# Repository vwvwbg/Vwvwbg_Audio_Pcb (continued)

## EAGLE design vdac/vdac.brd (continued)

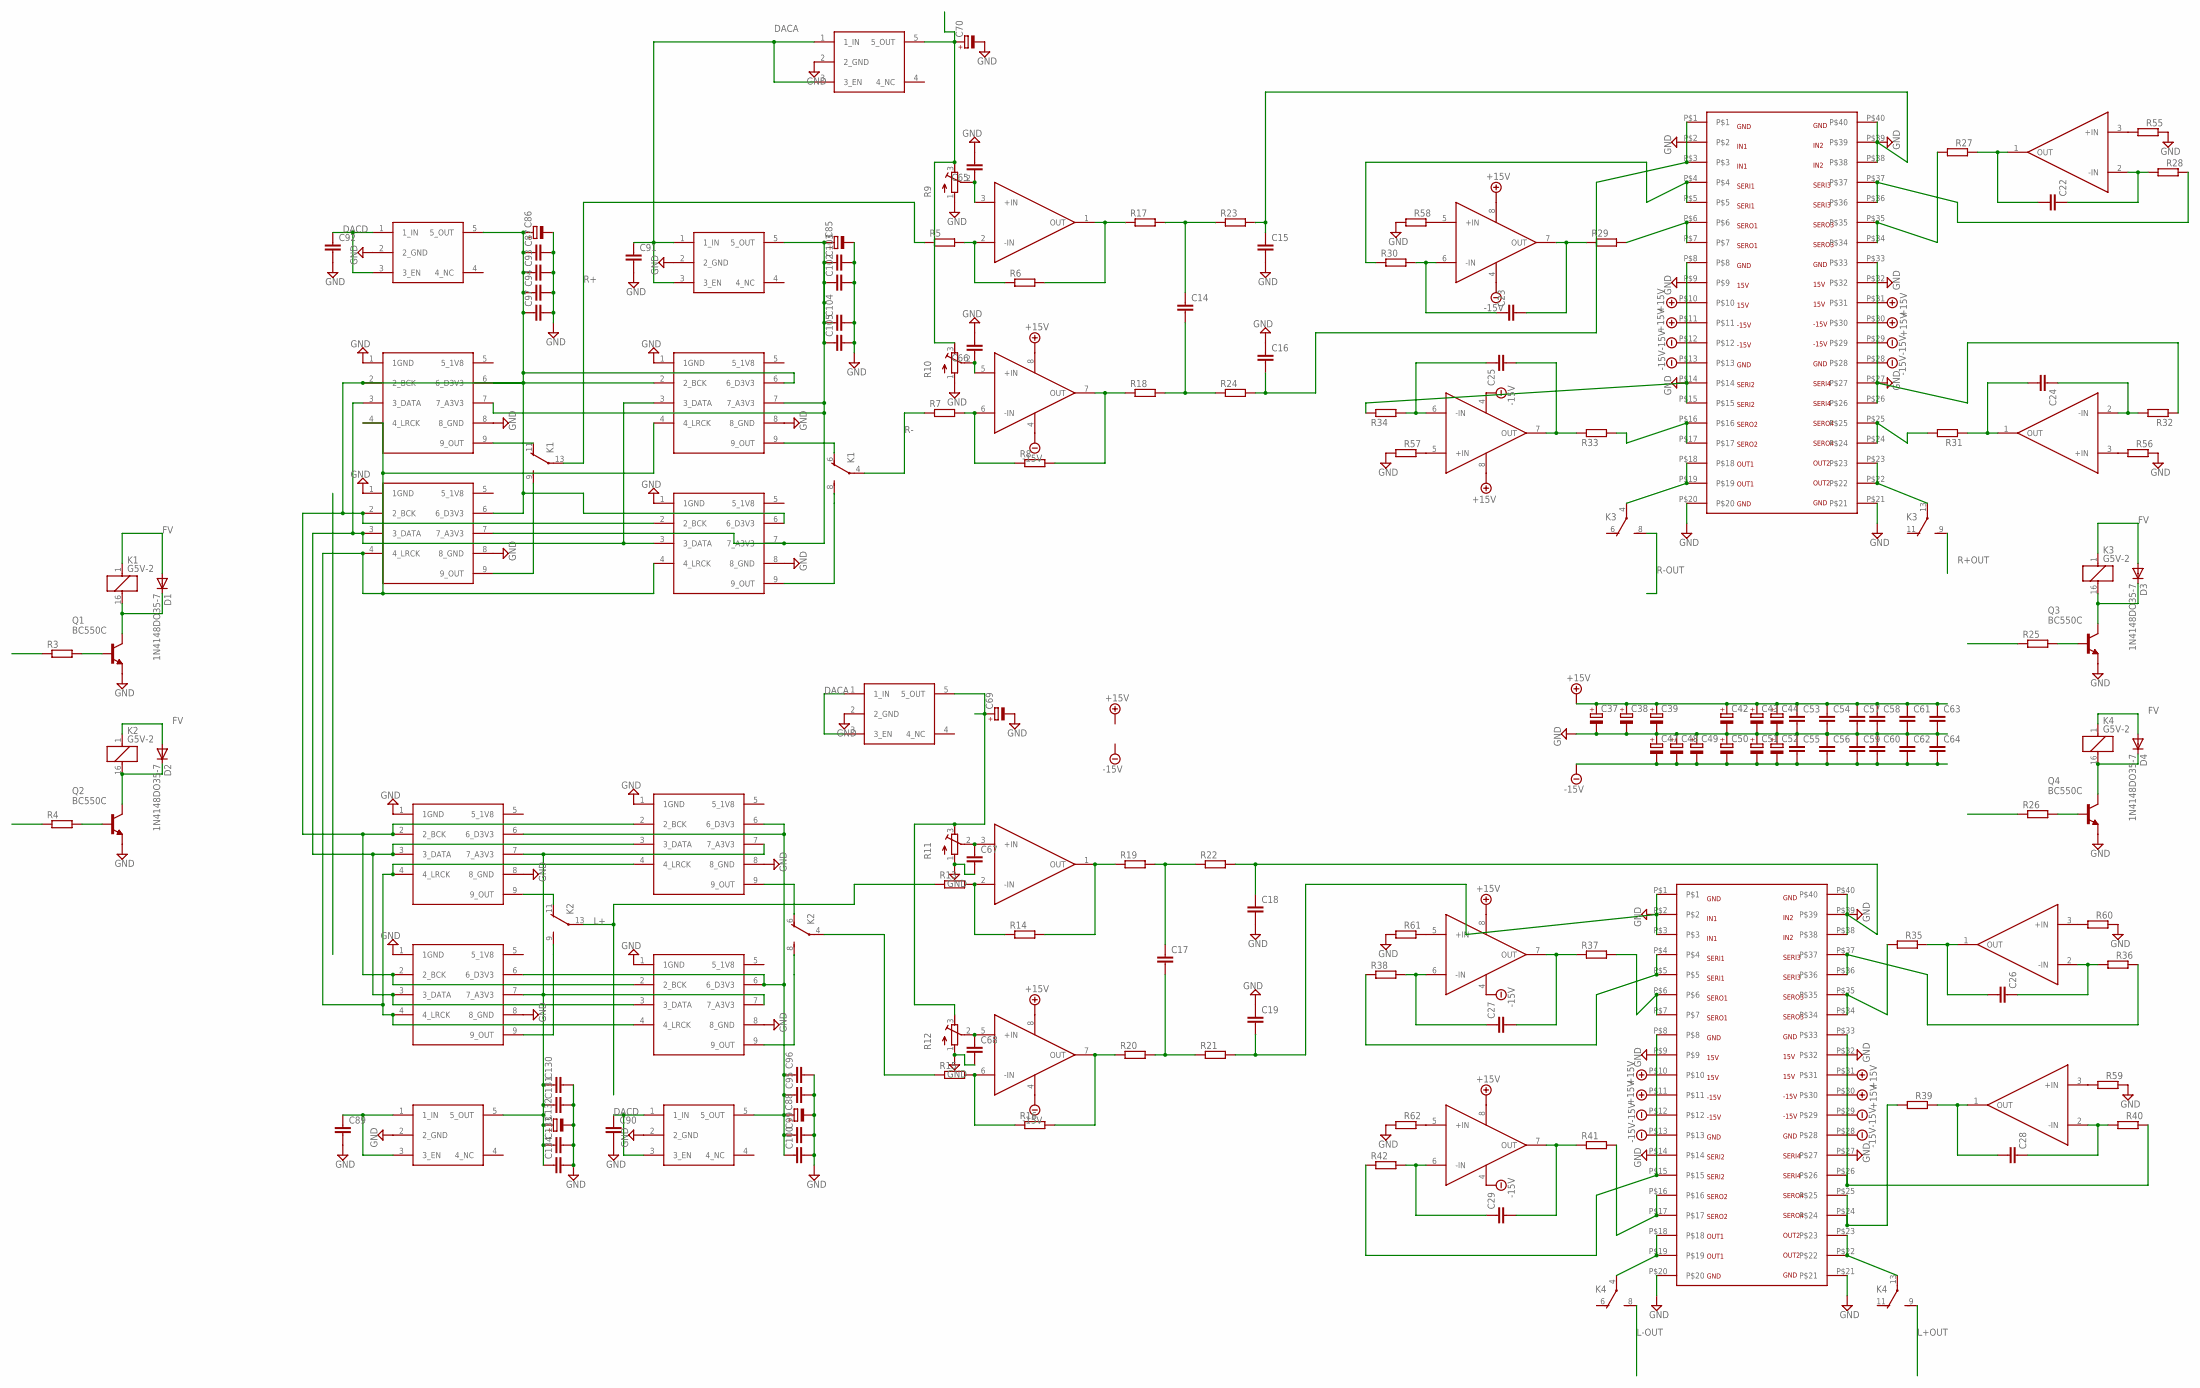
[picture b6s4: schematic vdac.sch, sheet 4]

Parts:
C14, C15, C16, C17, C18, C19: C-EUC0805; C0805
C22, C23, C24, C25, C26, C27, C28, C29, C65, C66, C67, C68, C87, C89, C90, C91, C92, C93, C94, C95, C96, C97, C99, C100, C102, C103, C104, C105, C130, C131, C133, C134: C-EUC1210; C1210
C37, C38, C39, C42, C43, C44, C47, C48, C49, C50, C51, C52, C69, C70, C85, C86, C88, C132: CPOL-EUSP-CAP-CX; SP-CAP-CX
C53, C54, C55, C56, C57, C58, C59, C60, C61, C62, C63, C64: C-EUC1206; C1206
D1, D2, D3, D4: 1N4148DO35-7; DO35-7
DSDL+: R2R
DSDL-: R2R
DSDR+: R2R
DSDR-: R2R
K1, K2, K3, K4: G5V-2
L+: R2R
L-: R2R
Q1, Q2, Q3, Q4: BC550C; TO92-EBC
R3, R4, R5, R6, R7, R8, R13, R14, R15, R16, R17, R18, R19, R20, R21, R22, R23, R24, R25, R26, R27, R28, R29, R30, R31, R32, R33, R34, R35, R36, R37, R38, R39, R40, R41, R42, R55, R56, R57, R58, R59, R60, R61, R62: R-EU_MELF0204W; MINI_MELF-0204W
R9, R10, R11, R12: R-TRIMM3296W; RTRIM3296W
R+: R2R
R-: R2R
U$5, U$6, U$13, U$14, U$21, U$22: LME49720; DIL08
U$7, U$8, U$17, U$18, U$19, U$20: LP5907; SOT-23-5
U$9, U$11: VDACA

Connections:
+15V: C37.+, C38.+, C39.+, C42.+, C43.+, C44.+, C53.1, C54.1, C57.1, C58.1, C61.1, C63.1, U$5.8 (V+), U$6.8 (V+), U$9.P$9, U$9.P$10, U$9.P$31, U$9.P$32, U$11.P$9, U$11.P$10, U$11.P$31, U$11.P$32, U$13.8 (V+), U$14.8 (V+), U$21.8 (V+), U$22.8 (V+); also elsewhere on the board
-15V: C47.-, C48.-, C49.-, C50.-, C51.-, C52.-, C55.2, C56.2, C59.2, C60.2, C62.2, C64.2, U$5.4 (V-), U$6.4 (V-), U$9.P$11, U$9.P$12, U$9.P$29, U$9.P$30, U$11.P$11, U$11.P$12, U$11.P$29, U$11.P$30, U$13.4 (V-), U$14.4 (V-), U$21.4 (V-), U$22.4 (V-); also elsewhere on the board
BCK: DSDL+.2 (2_BCK), DSDL-.2 (2_BCK), DSDR+.2 (2_BCK), DSDR-.2 (2_BCK), L+.2 (2_BCK), L-.2 (2_BCK), R+.2 (2_BCK), R-.2 (2_BCK); also elsewhere on the board
DACA: C89.1, C91.1, U$7.1 (1_IN), U$7.3 (3_EN), U$8.1 (1_IN), U$8.3 (3_EN), U$18.1 (1_IN), U$18.3 (3_EN), U$19.1 (1_IN), U$19.3 (3_EN); also elsewhere on the board
DACD: C90.1, C92.1, U$17.1 (1_IN), U$17.3 (3_EN), U$20.1 (1_IN), U$20.3 (3_EN); also elsewhere on the board
DATA: DSDL+.3 (3_DATA), DSDL-.3 (3_DATA), DSDR+.3 (3_DATA), DSDR-.3 (3_DATA), L+.3 (3_DATA), L-.3 (3_DATA), R+.3 (3_DATA), R-.3 (3_DATA); also elsewhere on the board
FDSDON1: R3.1; also elsewhere on the board
FDSDON2: R4.1; also elsewhere on the board
FV: D1.A, D2.A, D3.A, D4.A, K1.1, K2.1, K3.1, K4.1; also elsewhere on the board
GND: C15.2, C16.1, C18.2, C19.1, C37.-, C38.-, C39.-, C42.-, C43.-, C44.-, C47.+, C48.+, C49.+, C50.+, C51.+, C52.+, C53.2, C54.2, C55.1, C56.1, C57.2, C58.2, C59.1, C60.1, C61.2, C62.1, C63.2, C64.1, C65.2, C66.2, C67.2, C68.2, C69.-, C70.-, C85.-, C86.-, C87.2, C88.-, C89.2, C90.2, C91.2, C92.2, C93.2, C94.2, C95.2, C96.2, C97.2, C99.2, C100.2, C102.2, C103.2, C104.2, C105.2, C130.2, C131.2, C132.-, C133.2, C134.2, DSDL+.1 (1GND), DSDL+.8 (8_GND), DSDL-.1 (1GND), DSDL-.8 (8_GND), DSDR+.1 (1GND), DSDR+.8 (8_GND), DSDR-.1 (1GND), DSDR-.8 (8_GND), L+.1 (1GND), L+.8 (8_GND), L-.1 (1GND), L-.8 (8_GND), Q1.E, Q2.E, Q3.E, Q4.E, R9.1 (A), R10.1 (A), R11.1 (A), R12.1 (A), R55.1, R56.1, R57.2, R58.2, R59.1, R60.1, R61.2, R62.2, R+.1 (1GND), R+.8 (8_GND), R-.1 (1GND), R-.8 (8_GND), U$7.2 (2_GND), U$8.2 (2_GND), U$9.P$1, U$9.P$8, U$9.P$13, U$9.P$20, U$9.P$21, U$9.P$28, U$9.P$33, U$9.P$40, U$11.P$1, U$11.P$8, U$11.P$13, U$11.P$20, U$11.P$21, U$11.P$28, U$11.P$33, U$11.P$40, U$17.2 (2_GND), U$18.2 (2_GND), U$19.2 (2_GND), U$20.2 (2_GND); also elsewhere on the board
L+: K2.13, R13.1
L+OUT: K4.9 (S); also elsewhere on the board
L-: K2.4, R15.1
L-OUT: K4.8 (S); also elsewhere on the board
LC: R26.1; also elsewhere on the board
LRCK: DSDL+.4 (4_LRCK), DSDL-.4 (4_LRCK), DSDR+.4 (4_LRCK), DSDR-.4 (4_LRCK), L+.4 (4_LRCK), L-.4 (4_LRCK), R+.4 (4_LRCK), R-.4 (4_LRCK); also elsewhere on the board
unnamed: K1.11 (O), R+.9 (9_OUT)
unnamed: DSDR+.9 (9_OUT), K1.9 (S)
unnamed: K1.6 (O), R-.9 (9_OUT)
unnamed: DSDR-.9 (9_OUT), K1.8 (S)
unnamed: K2.11 (O), L+.9 (9_OUT)
unnamed: K2.6 (O), L-.9 (9_OUT)
unnamed: DSDL-.9 (9_OUT), K2.8 (S)
unnamed: DSDL+.9 (9_OUT), K2.9 (S)
unnamed: Q1.B, R3.2
unnamed: Q2.B, R4.2
unnamed: C130.1, C131.1, C132.+, C133.1, C134.1, DSDL+.7 (7_A3V3), DSDL-.7 (7_A3V3), L+.7 (7_A3V3), L-.7 (7_A3V3), U$19.5 (5_OUT)
unnamed: C85.+, C102.1, C103.1, C104.1, C105.1, DSDR+.7 (7_A3V3), DSDR-.7 (7_A3V3), R+.7 (7_A3V3), R-.7 (7_A3V3), U$18.5 (5_OUT)
unnamed: C86.+, C87.1, C93.1, C94.1, C97.1, DSDR+.6 (6_D3V3), DSDR-.6 (6_D3V3), R+.6 (6_D3V3), R-.6 (6_D3V3), U$17.5 (5_OUT)
unnamed: C88.+, C95.1, C96.1, C99.1, C100.1, DSDL+.6 (6_D3V3), DSDL-.6 (6_D3V3), L+.6 (6_D3V3), L-.6 (6_D3V3), U$20.5 (5_OUT)
unnamed: R7.2, R8.1, U$5.6 (-IN)
unnamed: D2.C, K2.16 (2), Q2.C
unnamed: D1.C, K1.16 (2), Q1.C
unnamed: R8.2, R18.1, U$5.7 (OUT)
unnamed: R5.2, R6.1, U$5.2 (-IN)
unnamed: R6.2, R17.1, U$5.1 (OUT)
unnamed: C67.1, R11.2 (S), U$6.3 (+IN)
unnamed: C65.1, R9.2 (S), U$5.3 (+IN)
unnamed: C66.1, R10.2 (S), U$5.5 (+IN)
unnamed: C70.+, R9.3 (E), R10.3 (E), U$7.5 (5_OUT)
unnamed: C68.1, R12.2 (S), U$6.5 (+IN)
unnamed: C69.+, R11.3 (E), R12.3 (E), U$8.5 (5_OUT)
unnamed: R13.2, R14.1, U$6.2 (-IN)
unnamed: R15.2, R16.1, U$6.6 (-IN)
unnamed: C17.1, R19.2, R22.1
unnamed: R16.2, R20.1, U$6.7 (OUT)
unnamed: R14.2, R19.1, U$6.1 (OUT)
unnamed: C17.2, R20.2, R21.1
unnamed: C18.1, R22.2, U$9.P$38, U$9.P$39
unnamed: C19.2, R21.2, U$9.P$2, U$9.P$3
unnamed: C14.2, R18.2, R24.1
unnamed: C16.2, R24.2, U$11.P$2, U$11.P$3
unnamed: C14.1, R17.2, R23.1
unnamed: C15.1, R23.2, U$11.P$38, U$11.P$39
unnamed: Q3.B, R25.2
unnamed: Q4.B, R26.2
unnamed: D4.C, K4.16 (2), Q4.C
unnamed: D3.C, K3.16 (2), Q3.C
unnamed: C22.1, R28.2, U$13.2 (-IN)
unnamed: C23.1, R30.2, U$13.6 (-IN)
unnamed: C23.2, R29.1, U$13.7 (OUT)
unnamed: C22.2, R27.1, U$13.1 (OUT)
unnamed: C24.1, R32.2, U$14.2 (-IN)
unnamed: C25.1, R34.2, U$14.6 (-IN)
unnamed: C25.2, R33.1, U$14.7 (OUT)
unnamed: C24.2, R31.1, U$14.1 (OUT)
unnamed: C26.1, R36.2, U$21.2 (-IN)
unnamed: C27.1, R38.2, U$21.6 (-IN)
unnamed: C27.2, R37.1, U$21.7 (OUT)
unnamed: C26.2, R35.1, U$21.1 (OUT)
unnamed: C28.1, R40.2, U$22.2 (-IN)
unnamed: C29.1, R42.2, U$22.6 (-IN)
unnamed: C29.2, R41.1, U$22.7 (OUT)
unnamed: C28.2, R39.1, U$22.1 (OUT)
unnamed: K4.4, U$9.P$18, U$9.P$19
unnamed: R29.2, U$11.P$6, U$11.P$7
unnamed: R33.2, U$11.P$16, U$11.P$17
unnamed: R34.1, U$11.P$14, U$11.P$15
unnamed: R30.1, U$11.P$4, U$11.P$5
unnamed: R27.2, U$11.P$34, U$11.P$35
unnamed: R28.1, U$11.P$36, U$11.P$37
unnamed: R31.2, U$11.P$24, U$11.P$25
unnamed: R32.1, U$11.P$26, U$11.P$27
unnamed: R41.2, U$9.P$16, U$9.P$17
unnamed: R42.1, U$9.P$14, U$9.P$15
unnamed: R37.2, U$9.P$6, U$9.P$7
unnamed: R38.1, U$9.P$4, U$9.P$5
unnamed: R35.2, U$9.P$34, U$9.P$35
unnamed: R36.1, U$9.P$36, U$9.P$37
unnamed: R40.1, U$9.P$26, U$9.P$27
unnamed: R39.2, U$9.P$24, U$9.P$25
unnamed: K4.13, U$9.P$22, U$9.P$23
unnamed: K3.4, U$11.P$18, U$11.P$19
unnamed: K3.13, U$11.P$22, U$11.P$23
unnamed: R55.2, U$13.3 (+IN)
unnamed: R56.2, U$14.3 (+IN)
unnamed: R57.1, U$14.5 (+IN)
unnamed: R58.1, U$13.5 (+IN)
unnamed: R59.2, U$22.3 (+IN)
unnamed: R60.2, U$21.3 (+IN)
unnamed: R61.1, U$21.5 (+IN)
unnamed: R62.1, U$22.5 (+IN)
R+: K1.13, R5.1
R+OUT: K3.9 (S); also elsewhere on the board
R-: K1.4, R7.1
R-OUT: K3.8 (S); also elsewhere on the board
RC: R25.1; also elsewhere on the board

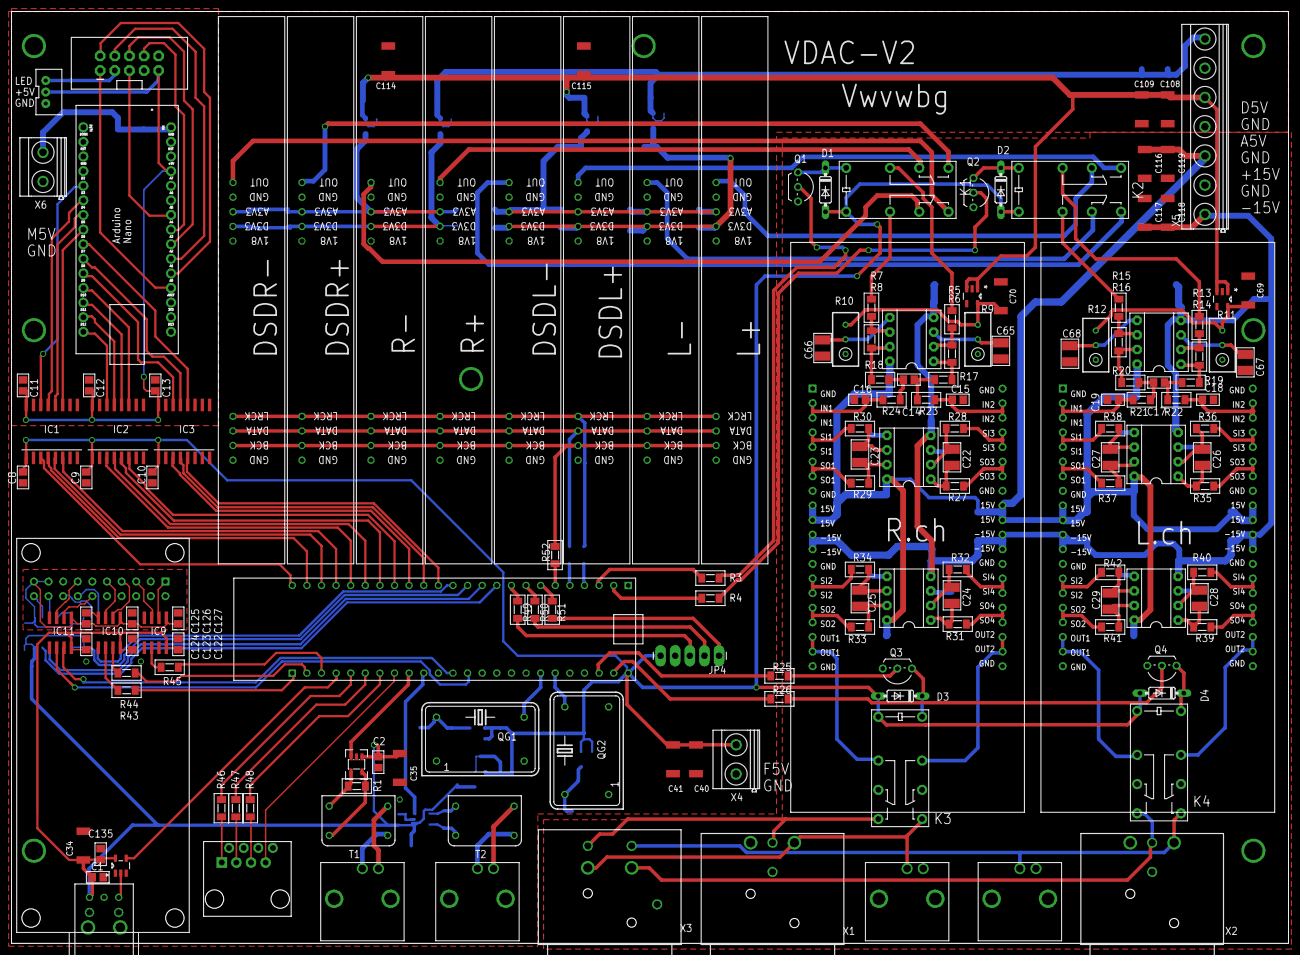
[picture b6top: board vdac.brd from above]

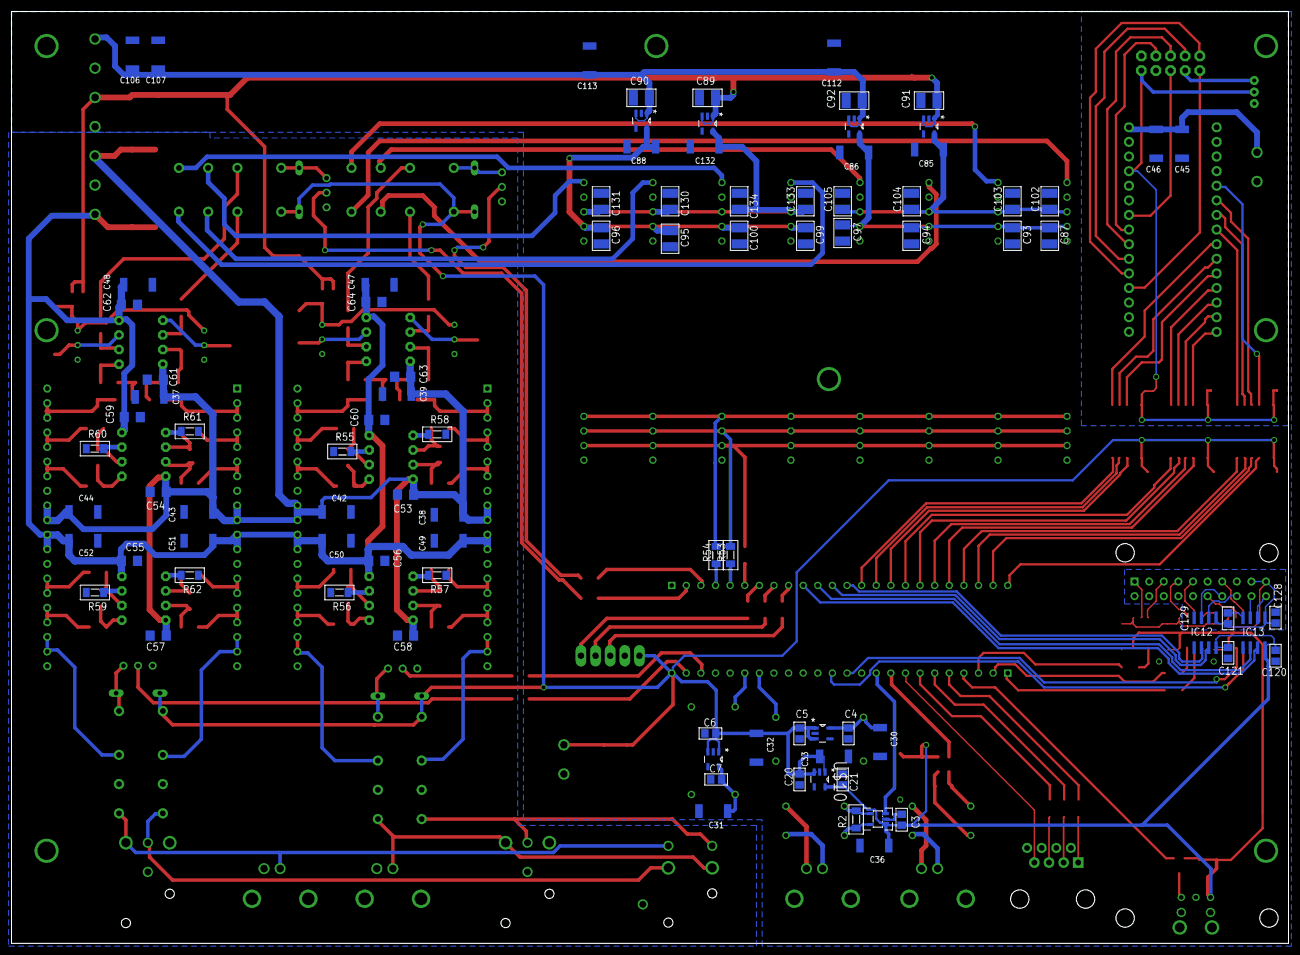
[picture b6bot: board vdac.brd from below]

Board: 2 copper layers, 222.0 x 162.0 mm, 249 parts (91 on the bottom side), 196 nets.

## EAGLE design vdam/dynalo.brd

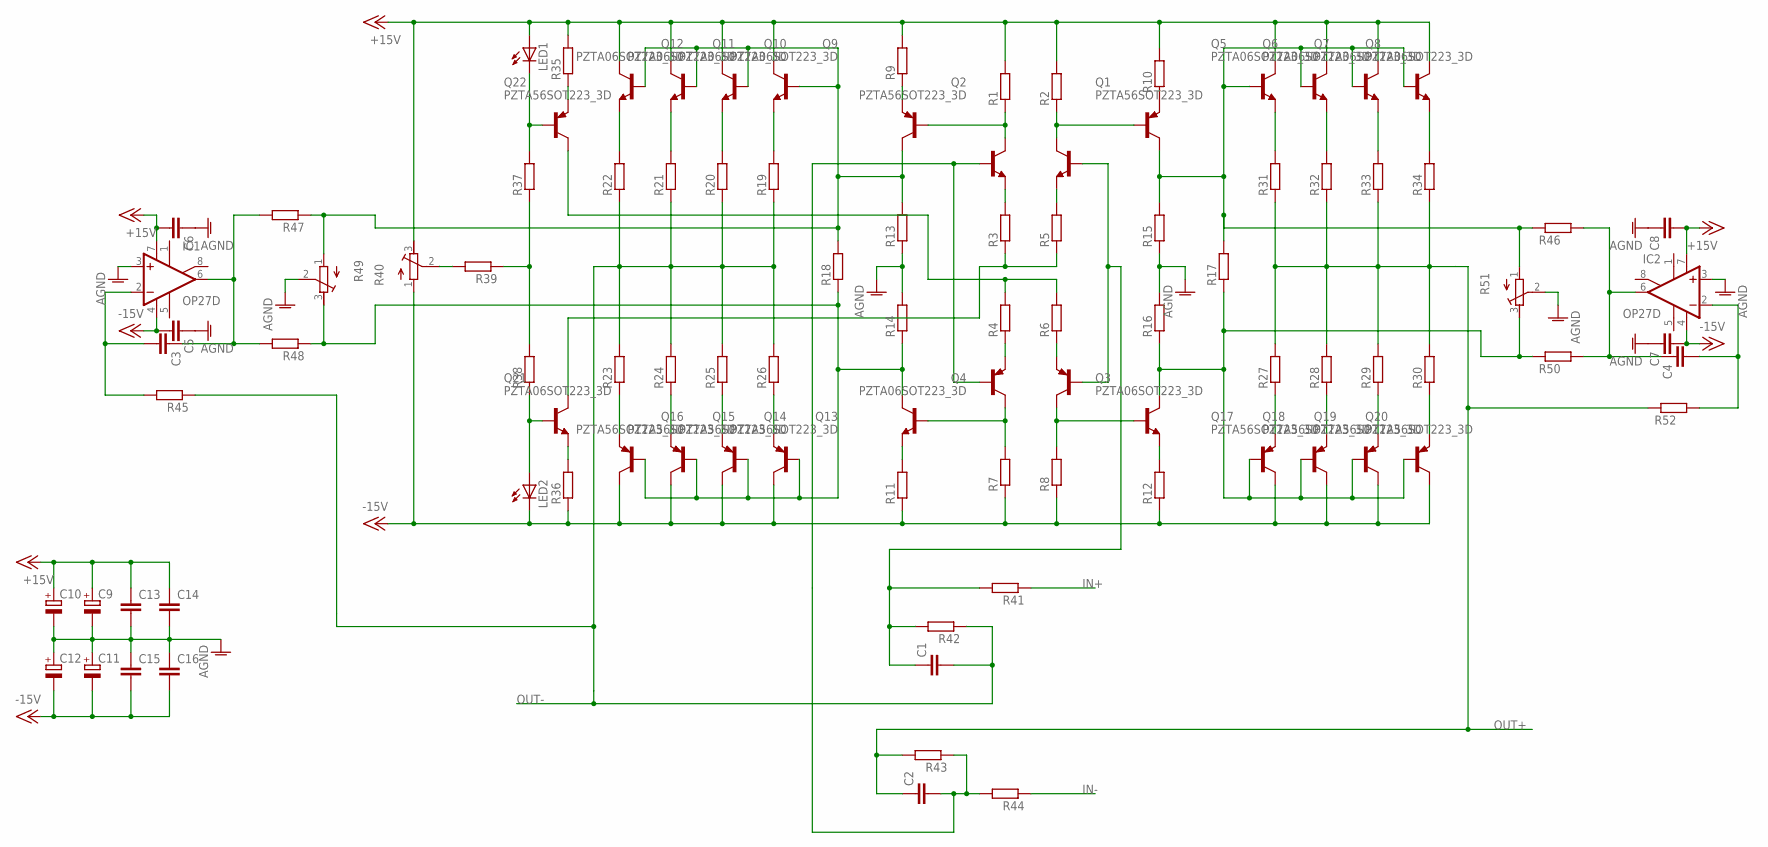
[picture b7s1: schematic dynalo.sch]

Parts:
C1, C2, C3, C4, C5, C6, C7, C8: C-EUC0805K; C0805K
C9, C10, C11, C12: CPOL-EUE5-10.5; E5-10,5
C13, C14, C15, C16: C-EU050-035X075; C050-035X075
IC1, IC2: OP27D; SO08
LED1, LED2: LED5MM
Q1, Q2, Q13, Q14, Q15, Q16, Q17, Q18, Q19, Q20, Q22: PZTA56SOT223_3D; SOT230P700X180-4
Q3, Q4, Q5, Q6, Q7, Q8, Q9, Q10, Q11, Q12, Q21: PZTA06SOT223_3D; SOT230P700X180-4
R1, R2, R3, R4, R5, R6, R7, R8, R9, R10, R11, R12, R13, R14, R15, R16, R17, R18, R19, R20, R21, R22, R23, R24, R25, R26, R27, R28, R29, R30, R31, R32, R33, R34, R35, R36, R37, R38, R41, R42, R43, R44, R45, R46, R47, R48, R50, R52: R-EU_MMA0204; RESMELF3413
R39: R-EU_MELF0204W; MINI_MELF-0204W
R40, R49, R51: R-TRIMM3296W; RTRIM3296W
U$1: TRANSISTOR-ARRAYS_THAT340THAT3403D; DIP762W53P254L1969H508Q14A

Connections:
+15V: C6.2, C8.2, C9.+, C10.+, C13.1, C14.1, IC1.7 (V+), IC2.7 (V+), LED1.A, Q5.2 (C), Q5.4 (C), Q6.2 (C), Q6.4 (C), Q7.2 (C), Q7.4 (C), Q8.2 (C), Q8.4 (C), Q9.2 (C), Q9.4 (C), Q10.2 (C), Q10.4 (C), Q11.2 (C), Q11.4 (C), Q12.2 (C), Q12.4 (C), R1.2, R2.2, R9.2, R10.2, R35.2, R40.3 (E)
-15V: C5.2, C7.2, C11.-, C12.-, C15.2, C16.2, IC1.4 (V-), IC2.4 (V-), LED2.K (C), Q13.2 (C), Q13.4 (C), Q14.2 (C), Q14.4 (C), Q15.2 (C), Q15.4 (C), Q16.2 (C), Q16.4 (C), Q17.2 (C), Q17.4 (C), Q18.2 (C), Q18.4 (C), Q19.2 (C), Q19.4 (C), Q20.2 (C), Q20.4 (C), R7.1, R8.1, R11.1, R12.1, R36.1, R40.1 (A)
AGND: C5.1, C6.1, C7.1, C8.1, C9.-, C10.-, C11.+, C12.+, C13.2, C14.2, C15.1, C16.1, IC1.3 (+IN), IC2.3 (+IN), R13.1, R14.2, R15.1, R16.2, R49.2 (S), R51.2 (S)
IN+: R41.1
IN-: R44.1
unnamed: R3.2, U$1.12 (E)
unnamed: R4.1, U$1.10 (E)
unnamed: R5.2, U$1.3 (E)
unnamed: R6.1, U$1.5 (E)
unnamed: Q22.2 (C), Q22.4 (C), R4.2, R6.2
unnamed: Q21.2 (C), Q21.4 (C), R3.1, R5.1
unnamed: Q2.1 (B), R1.1, U$1.14 (C)
unnamed: Q1.1 (B), R2.1, U$1.1 (C)
unnamed: Q3.1 (B), R8.2, U$1.7 (C)
unnamed: Q4.1 (B), R7.2, U$1.8 (C)
unnamed: Q2.3 (E), R9.1
unnamed: Q1.3 (E), R10.1
unnamed: Q4.3 (E), R11.2
unnamed: Q12.3 (E), R22.2
unnamed: Q11.3 (E), R21.2
unnamed: Q3.3 (E), R12.2
unnamed: Q2.2 (C), Q2.4 (C), Q9.1 (B), Q10.1 (B), Q11.1 (B), Q12.1 (B), R13.2, R18.2, R47.1, R49.1 (A)
unnamed: Q10.3 (E), R20.2
unnamed: Q4.2 (C), Q4.4 (C), Q13.1 (B), Q14.1 (B), Q15.1 (B), Q16.1 (B), R14.1, R18.1, R48.1, R49.3 (E)
unnamed: Q3.2 (C), Q3.4 (C), Q17.1 (B), Q18.1 (B), Q19.1 (B), Q20.1 (B), R16.1, R17.1, R50.1, R51.3 (E)
unnamed: Q9.3 (E), R19.2
unnamed: Q1.2 (C), Q1.4 (C), Q5.1 (B), Q6.1 (B), Q7.1 (B), Q8.1 (B), R15.2, R17.2, R46.1, R51.1 (A)
unnamed: C1.1, R41.2, R42.2, U$1.2 (B), U$1.6 (B)
unnamed: C2.2, R43.1, R44.2, U$1.9 (B), U$1.13 (B)
unnamed: Q13.3 (E), R26.1
unnamed: Q14.3 (E), R25.1
unnamed: Q15.3 (E), R24.1
unnamed: Q16.3 (E), R23.1
unnamed: Q17.3 (E), R27.1
unnamed: Q18.3 (E), R28.1
unnamed: Q19.3 (E), R29.1
unnamed: Q20.3 (E), R30.1
unnamed: Q8.3 (E), R34.2
unnamed: Q7.3 (E), R33.2
unnamed: Q6.3 (E), R32.2
unnamed: Q5.3 (E), R31.2
unnamed: C3.1, IC1.6 (OUT), R47.2, R48.2
unnamed: Q21.3 (E), R36.2
unnamed: LED2.A, Q21.1 (B), R38.1
unnamed: C3.2, IC1.2 (-IN), R45.2
unnamed: Q22.3 (E), R35.1
unnamed: LED1.K (C), Q22.1 (B), R37.2
unnamed: C4.1, IC2.6 (OUT), R46.2, R50.2
unnamed: R37.1, R38.2, R39.1
unnamed: R39.2, R40.2 (S)
unnamed: C4.2, IC2.2 (-IN), R52.2
OUT+: C2.1, R27.2, R28.2, R29.2, R30.2, R31.1, R32.1, R33.1, R34.1, R43.2, R52.1
OUT-: C1.2, R19.1, R20.1, R21.1, R22.1, R23.2, R24.2, R25.2, R26.2, R42.1, R45.1

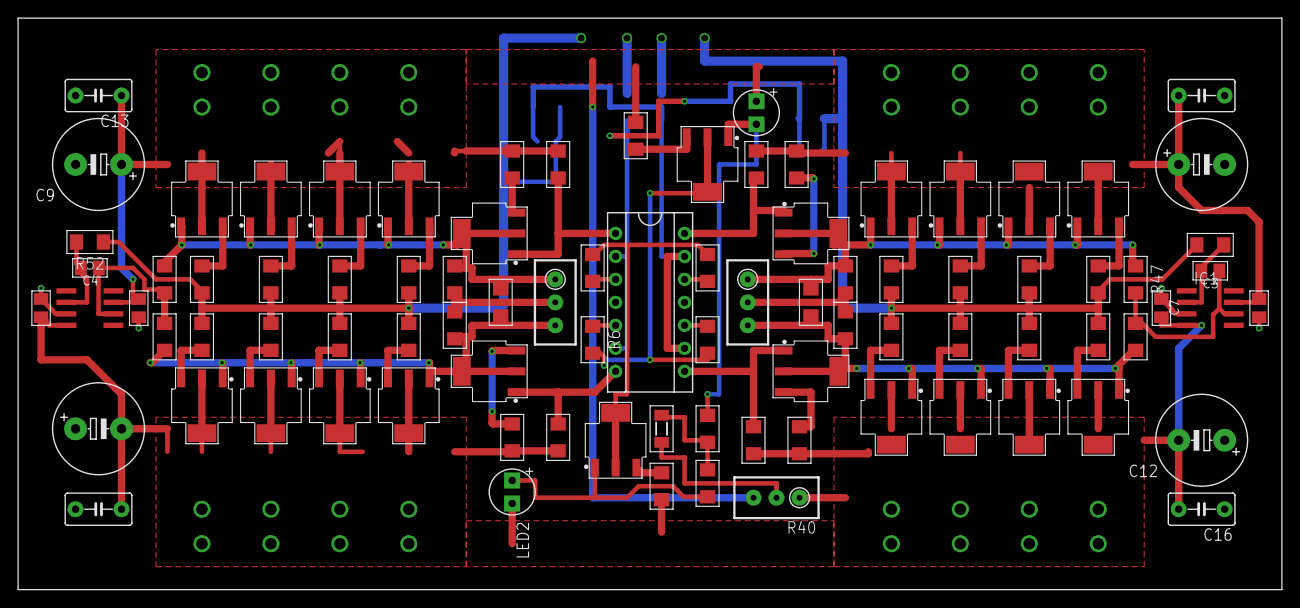
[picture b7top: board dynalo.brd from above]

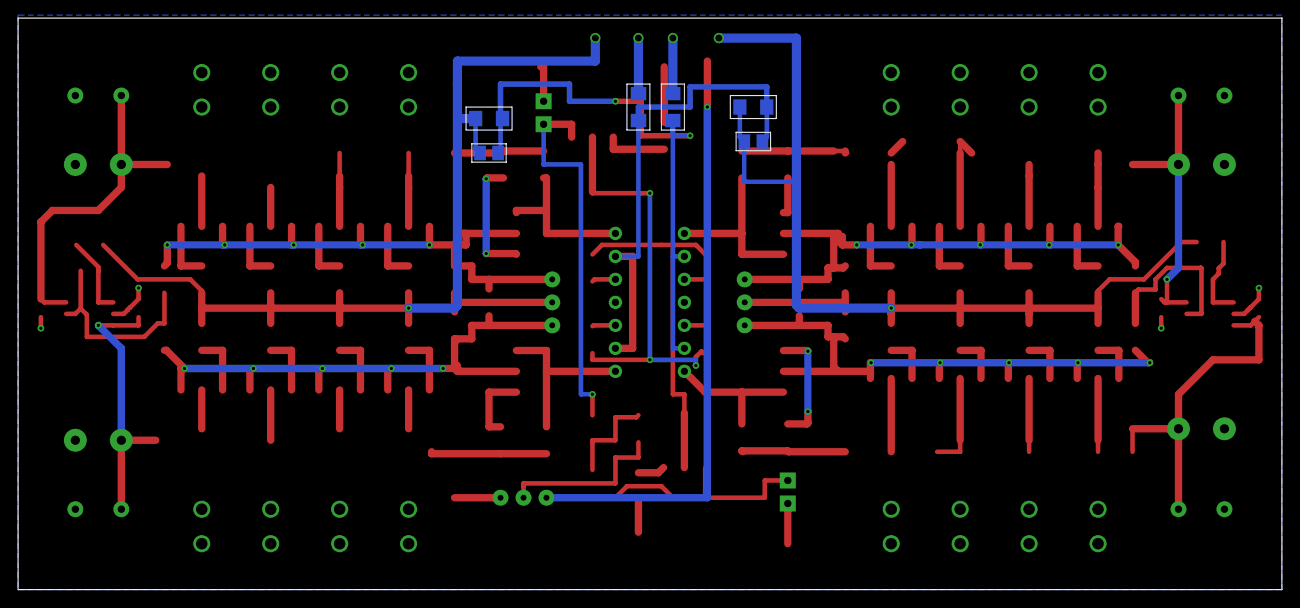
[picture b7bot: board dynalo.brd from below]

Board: 2 copper layers, 139.7 x 63.2 mm, 95 parts (6 on the bottom side), 51 nets.
